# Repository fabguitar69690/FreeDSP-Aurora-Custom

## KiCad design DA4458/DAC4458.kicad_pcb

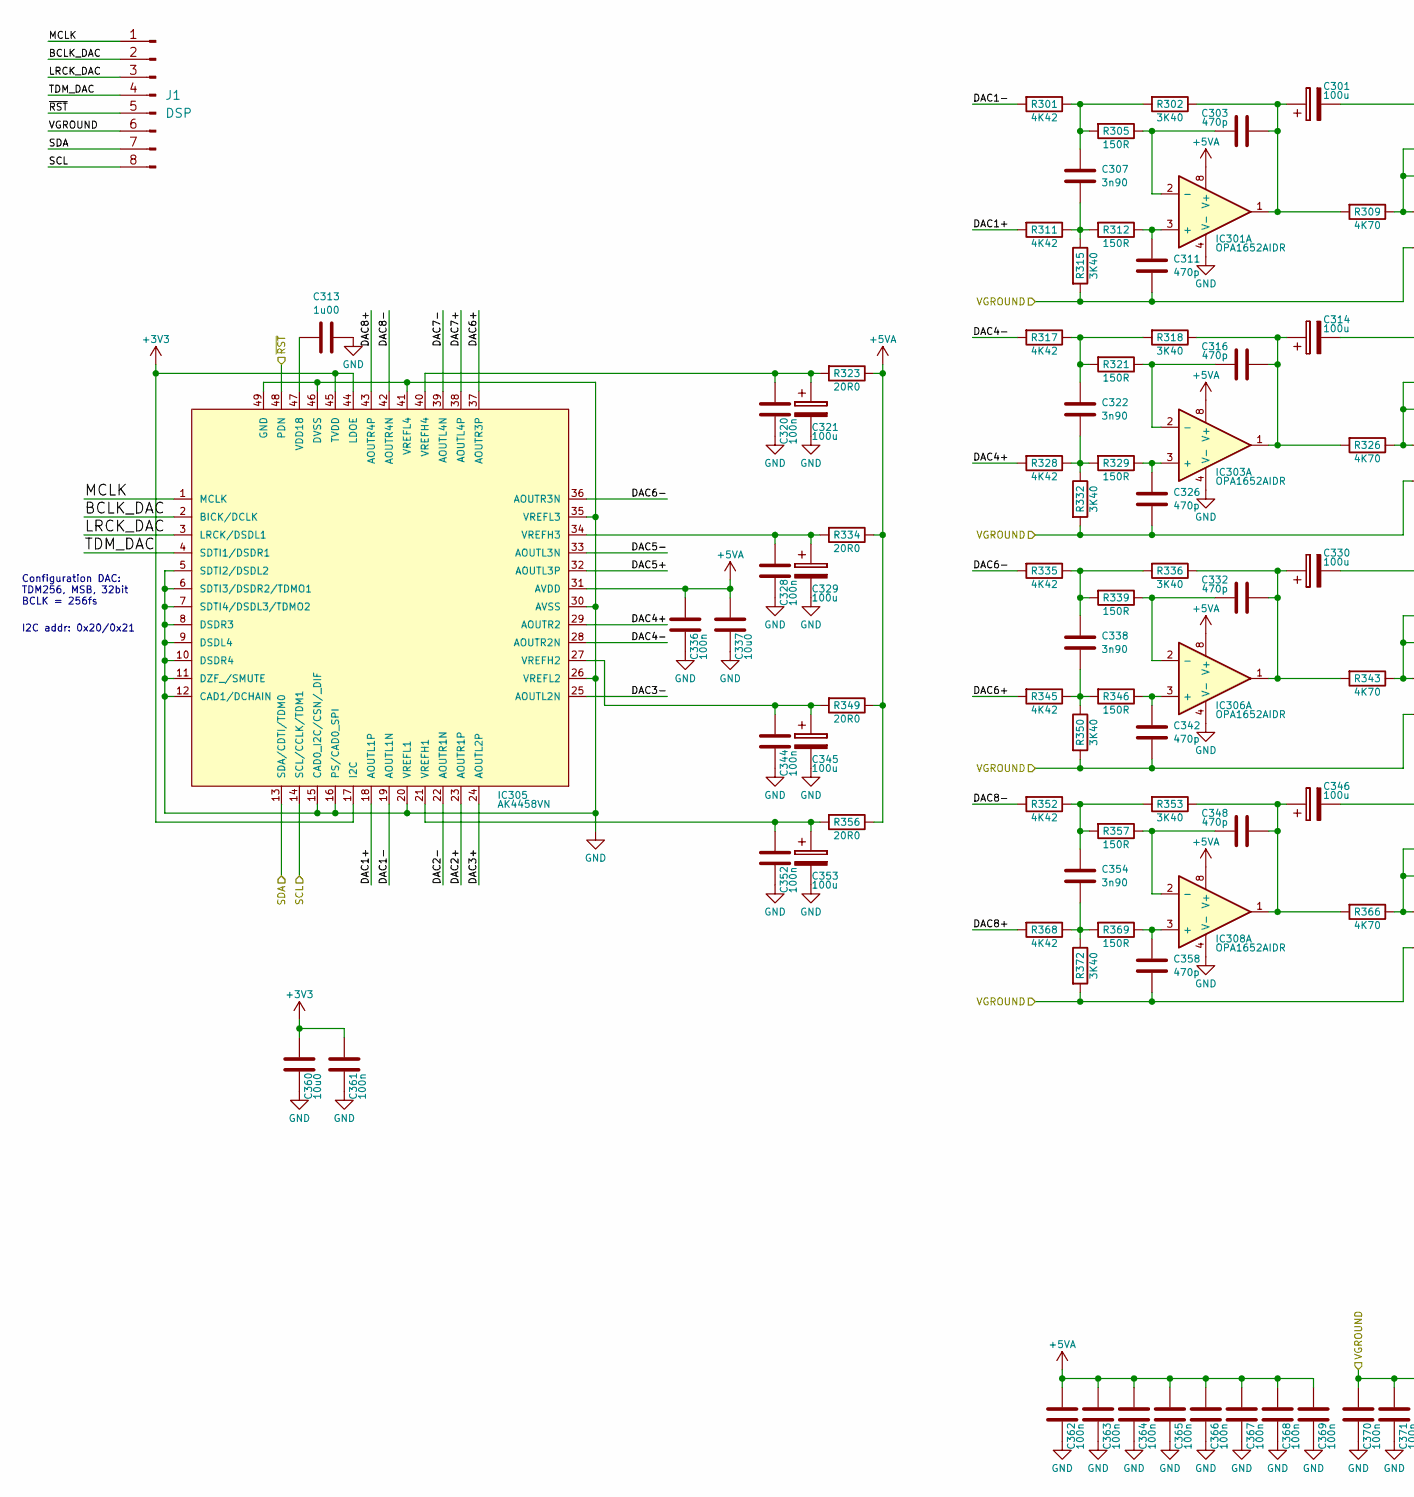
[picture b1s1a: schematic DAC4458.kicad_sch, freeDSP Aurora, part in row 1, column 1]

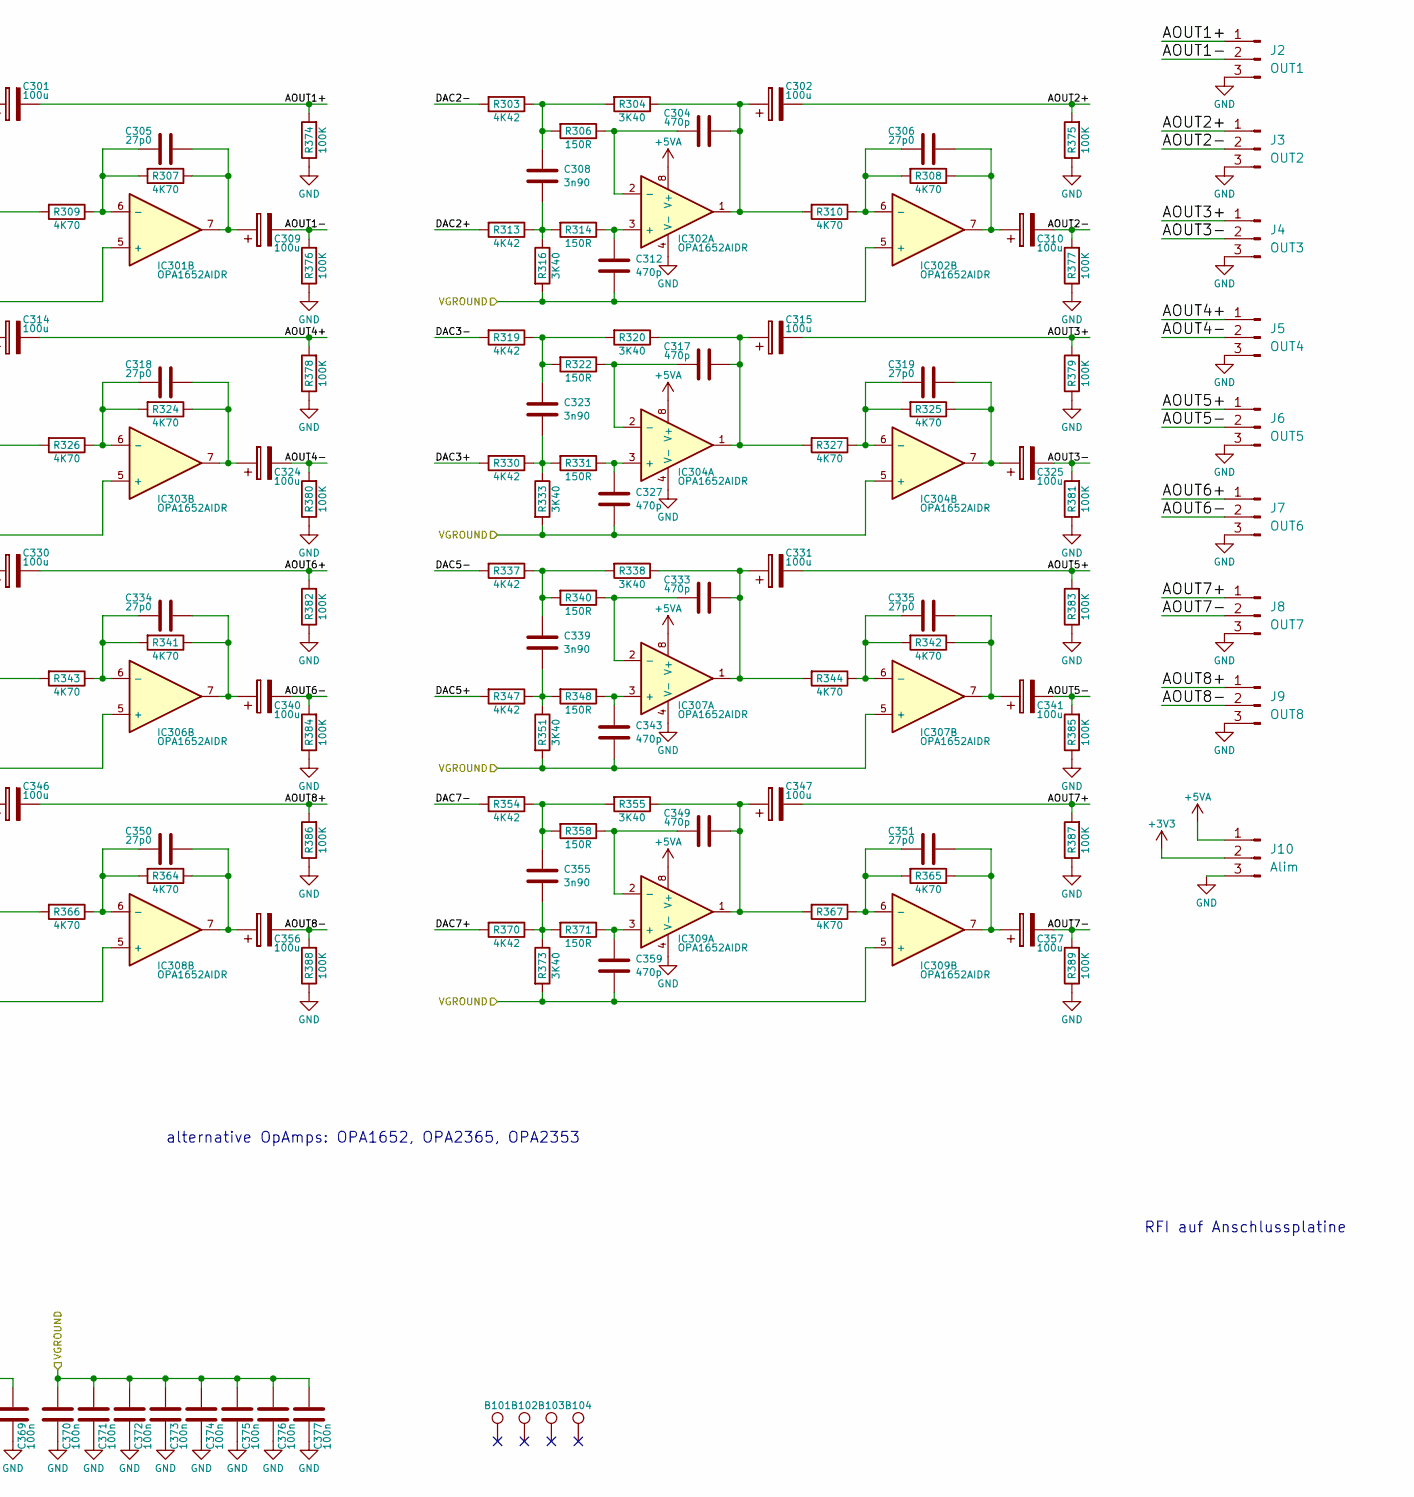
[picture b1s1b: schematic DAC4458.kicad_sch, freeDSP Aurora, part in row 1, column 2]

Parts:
B101, B102, B103, B104: TEST_1P; MountingHole_3.2mm_M3_DIN965_Pad
C301, C302, C309, C310, C314, C315, C321, C324, C325, C329, C330, C331, C340, C341, C345, C346, C347, C353, C356, C357: CAP_100u_20%_25V_ALUM_RADIAL; RD2_D5_L11; digikey UVY1E101MDD-ND
C303, C304, C311, C312, C316, C317, C326, C327, C332, C333, C342, C343, C348, C349, C358, C359: CAP_470p_2%_50V_PPS_0805; C0805-X7R; digikey PCF1292CT-ND
C305, C306, C318, C319, C334, C335, C350, C351: CAP_27p0_50V_C0G_NP0_0805; C0805-X7R; digikey 399-1114-1-ND
C307, C308, C322, C323, C338, C339, C354, C355: CAP_3n90_5%_16V_PPS_0805; C0805-X7R; digikey PCF1191CT-ND
C313: CAP_1u00_16V_X7R_0805; C0805-X7R; digikey 311-1365-1-ND
C320, C328, C336, C344, C352, C361, C362, C363, C364, C365, C366, C367, C368, C369, C370, C371, C372, C373, C374, C375, C376, C377: CAP_100n_50V_X7R_0805; C0805-X7R; digikey 399-1170-1-ND
C337, C360: CAP_10u0_25V_X5R_0805; C0805-X7R; digikey 490-10748-1-ND
IC301, IC302, IC303, IC304, IC306, IC307, IC308, IC309: IC_OPA1652AIDR; SOIC8_3.9x4.9mm_Pitch1.27mm; digikey 296-39101-1-ND
IC305: IC_AK4458VN; QFN48_7x7mm_Pitch0.5mm_EP_Handsoldering; digikey 974-1082-1-ND
J1: DSP; PinHeader_1x08_P2.54mm_Vertical
J2: OUT1; PinHeader_1x03_P2.54mm_Vertical
J3: OUT2; PinHeader_1x03_P2.54mm_Vertical
J4: OUT3; PinHeader_1x03_P2.54mm_Vertical
J5: OUT4; PinHeader_1x03_P2.54mm_Vertical
J6: OUT5; PinHeader_1x03_P2.54mm_Vertical
J7: OUT6; PinHeader_1x03_P2.54mm_Vertical
J8: OUT7; PinHeader_1x03_P2.54mm_Vertical
J9: OUT8; PinHeader_1x03_P2.54mm_Vertical
J10: Alim; PinHeader_1x03_P2.54mm_Vertical
R301, R303, R311, R313, R317, R319, R328, R330, R335, R337, R345, R347, R352, R354, R368, R370: RES_4K42_0.5%_0.1W_Thin_0805; C0805-RES; digikey RR12P4.42KDCT-ND
R302, R304, R315, R316, R318, R320, R332, R333, R336, R338, R350, R351, R353, R355, R372, R373: RES_3K40_0.5%_0.1W_Thin_0805; C0805-RES; digikey RR12P3.4KDCT-ND
R305, R306, R312, R314, R321, R322, R329, R331, R339, R340, R346, R348, R357, R358, R369, R371: RES_150R_1%_0.25W_Thin_0805; C0805-RES; digikey RNCP0805FTD150RCT-ND
R307, R308, R309, R310, R324, R325, R326, R327, R341, R342, R343, R344, R364, R365, R366, R367: RES_4K70_1%_0.125W_Thin_0805; C0805-RES; digikey YAG3364CT-ND
R323, R334, R349, R356: RES_20R0_1%_0.125W_Thick_0805; C0805-RES; digikey 311-20.0CRCT-ND
R374, R375, R376, R377, R378, R379, R380, R381, R382, R383, R384, R385, R386, R387, R388, R389: RES_100K_1%_0.125W_Thick_0805; C0805-RES; digikey 311-100KCRCT-ND

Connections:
+3V3: C360.1, C361.1, IC305.17 (I2C), IC305.44 (LDOE), IC305.45 (TVDD), J10.2
+5VA: C336.1, C337.1, C362.1, C363.1, C364.1, C365.1, C366.1, C367.1, C368.1, C369.1, IC301.8 (V+), IC302.8 (V+), IC303.8 (V+), IC304.8 (V+), IC305.31 (AVDD), IC306.8 (V+), IC307.8 (V+), IC308.8 (V+), IC309.8 (V+), J10.1, R323.1, R334.1, R349.1, R356.1
/AOUT1+: C301.2, J2.1, R374.2
/AOUT1-: C309.2, J2.2, R376.2
/AOUT2+: C302.2, J3.1, R375.2
/AOUT2-: C310.2, J3.2, R377.2
/AOUT3+: C315.2, J4.1, R379.2
/AOUT3-: C325.2, J4.2, R381.2
/AOUT4+: C314.2, J5.1, R378.2
/AOUT4-: C324.2, J5.2, R380.2
/AOUT5+: C331.2, J6.1, R383.2
/AOUT5-: C341.2, J6.2, R385.2
/AOUT6+: C330.2, J7.1, R382.2
/AOUT6-: C340.2, J7.2, R384.2
/AOUT7+: C347.2, J8.1, R387.2
/AOUT7-: C357.2, J8.2, R389.2
/AOUT8+: C346.2, J9.1, R386.2
/AOUT8-: C356.2, J9.2, R388.2
/BCLK_DAC: IC305.2 (BICK/DCLK), J1.2
/DAC1+: IC305.18 (AOUTL1P), R311.2
/DAC1-: IC305.19 (AOUTL1N), R301.2
/DAC2+: IC305.23 (AOUTR1P), R313.2
/DAC2-: IC305.22 (AOUTR1N), R303.2
/DAC3+: IC305.24 (AOUTL2P), R330.2
/DAC3-: IC305.25 (AOUTL2N), R319.2
/DAC4+: IC305.29 (AOUTR2), R328.2
/DAC4-: IC305.28 (AOUTR2N), R317.2
/DAC5+: IC305.32 (AOUTL3P), R347.2
/DAC5-: IC305.33 (AOUTL3N), R337.2
/DAC6+: IC305.37 (AOUTR3P), R345.2
/DAC6-: IC305.36 (AOUTR3N), R335.2
/DAC7+: IC305.38 (AOUTL4P), R370.2
/DAC7-: IC305.39 (AOUTL4N), R354.2
/DAC8+: IC305.43 (AOUTR4P), R368.2
/DAC8-: IC305.42 (AOUTR4N), R352.2
/LRCK_DAC: IC305.3 (LRCK/DSDL1), J1.3
/MCLK: IC305.1 (MCLK), J1.1
/SCL: IC305.14 (SCL/CCLK/TDM1), J1.8
/SDA: IC305.13 (SDA/CDTI/TDM0), J1.7
/TDM_DAC: IC305.4 (SDTI1/DSDR1), J1.4
/VGROUND: C311.2, C312.2, C326.2, C327.2, C342.2, C343.2, C358.2, C359.2, C370.1, C371.1, C372.1, C373.1, C374.1, C375.1, C376.1, C377.1, IC301.5 (+), IC302.5 (+), IC303.5 (+), IC304.5 (+), IC306.5 (+), IC307.5 (+), IC308.5 (+), IC309.5 (+), J1.6, R315.2, R316.2, R332.2, R333.2, R350.2, R351.2, R372.2, R373.2
/~RST: IC305.48 (PDN), J1.5
GND: C313.2, C320.2, C321.2, C328.2, C329.2, C336.2, C337.2, C344.2, C345.2, C352.2, C353.2, C360.2, C361.2, C362.2, C363.2, C364.2, C365.2, C366.2, C367.2, C368.2, C369.2, C370.2, C371.2, C372.2, C373.2, C374.2, C375.2, C376.2, C377.2, IC301.4 (V-), IC302.4 (V-), IC303.4 (V-), IC304.4 (V-), IC305.5 (SDTI2/DSDL2), IC305.6 (SDTI3/DSDR2/TDMO1), IC305.7 (SDTI4/DSDL3/TDMO2), IC305.8 (DSDR3), IC305.9 (DSDL4), IC305.10 (DSDR4), IC305.11 (DZF_/SMUTE), IC305.12 (CAD1/DCHAIN), IC305.15 (CAD0_I2C/CSN/_DIF), IC305.16 (PS/CAD0_SPI), IC305.20 (VREFL1), IC305.26 (VREFL2), IC305.30 (AVSS), IC305.35 (VREFL3), IC305.41 (VREFL4), IC305.46 (DVSS), IC305.49 (GND), IC306.4 (V-), IC307.4 (V-), IC308.4 (V-), IC309.4 (V-), J2.3, J3.3, J4.3, J5.3, J6.3, J7.3, J8.3, J9.3, J10.3, R374.1, R375.1, R376.1, R377.1, R378.1, R379.1, R380.1, R381.1, R382.1, R383.1, R384.1, R385.1, R386.1, R387.1, R388.1, R389.1
unnamed: C301.1, C303.1, IC301.1, R302.1, R309.2
unnamed: C302.1, C304.1, IC302.1, R304.1, R310.2
unnamed: C303.2, IC301.2 (-), R305.1
unnamed: C304.2, IC302.2 (-), R306.1
unnamed: C305.1, C309.1, IC301.7, R307.1
unnamed: C305.2, IC301.6 (-), R307.2, R309.1
unnamed: C306.1, C310.1, IC302.7, R308.1
unnamed: C306.2, IC302.6 (-), R308.2, R310.1
unnamed: C307.1, R301.1, R302.2, R305.2
unnamed: C307.2, R311.1, R312.2, R315.1
unnamed: C308.1, R303.1, R304.2, R306.2
unnamed: C308.2, R313.1, R314.2, R316.1
unnamed: C311.1, IC301.3 (+), R312.1
unnamed: C312.1, IC302.3 (+), R314.1
unnamed: C313.1, IC305.47 (VDD18)
unnamed: C314.1, C316.1, IC303.1, R318.1, R326.2
unnamed: C315.1, C317.1, IC304.1, R320.1, R327.2
unnamed: C316.2, IC303.2 (-), R321.1
unnamed: C317.2, IC304.2 (-), R322.1
unnamed: C318.1, C324.1, IC303.7, R324.1
unnamed: C318.2, IC303.6 (-), R324.2, R326.1
unnamed: C319.1, C325.1, IC304.7, R325.1
unnamed: C319.2, IC304.6 (-), R325.2, R327.1
unnamed: C320.1, C321.1, IC305.40 (VREFH4), R323.2
unnamed: C322.1, R317.1, R318.2, R321.2
unnamed: C322.2, R328.1, R329.2, R332.1
unnamed: C323.1, R319.1, R320.2, R322.2
unnamed: C323.2, R330.1, R331.2, R333.1
unnamed: C326.1, IC303.3 (+), R329.1
unnamed: C327.1, IC304.3 (+), R331.1
unnamed: C328.1, C329.1, IC305.34 (VREFH3), R334.2
unnamed: C330.1, C332.1, IC306.1, R336.1, R343.2
unnamed: C331.1, C333.1, IC307.1, R338.1, R344.2
unnamed: C332.2, IC306.2 (-), R339.1
unnamed: C333.2, IC307.2 (-), R340.1
unnamed: C334.1, C340.1, IC306.7, R341.1
unnamed: C334.2, IC306.6 (-), R341.2, R343.1
unnamed: C335.1, C341.1, IC307.7, R342.1
unnamed: C335.2, IC307.6 (-), R342.2, R344.1
unnamed: C338.1, R335.1, R336.2, R339.2
unnamed: C338.2, R345.1, R346.2, R350.1
unnamed: C339.1, R337.1, R338.2, R340.2
unnamed: C339.2, R347.1, R348.2, R351.1
unnamed: C342.1, IC306.3 (+), R346.1
unnamed: C343.1, IC307.3 (+), R348.1
unnamed: C344.1, C345.1, IC305.27 (VREFH2), R349.2
unnamed: C346.1, C348.1, IC308.1, R353.1, R366.2
unnamed: C347.1, C349.1, IC309.1, R355.1, R367.2
unnamed: C348.2, IC308.2 (-), R357.1
unnamed: C349.2, IC309.2 (-), R358.1
unnamed: C350.1, C356.1, IC308.7, R364.1
unnamed: C350.2, IC308.6 (-), R364.2, R366.1
unnamed: C351.1, C357.1, IC309.7, R365.1
unnamed: C351.2, IC309.6 (-), R365.2, R367.1
unnamed: C352.1, C353.1, IC305.21 (VREFH1), R356.2
unnamed: C354.1, R352.1, R353.2, R357.2
unnamed: C354.2, R368.1, R369.2, R372.1
unnamed: C355.1, R354.1, R355.2, R358.2
unnamed: C355.2, R370.1, R371.2, R373.1
unnamed: C358.1, IC308.3 (+), R369.1
unnamed: C359.1, IC309.3 (+), R371.1

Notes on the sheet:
alternative OpAmps: OPA1652, OPA2365, OPA2353
RFI auf Anschlussplatine
Configuration DAC: TDM256, MSB, 32bit BCLK = 256fs
I2C addr: 0x20/0x21

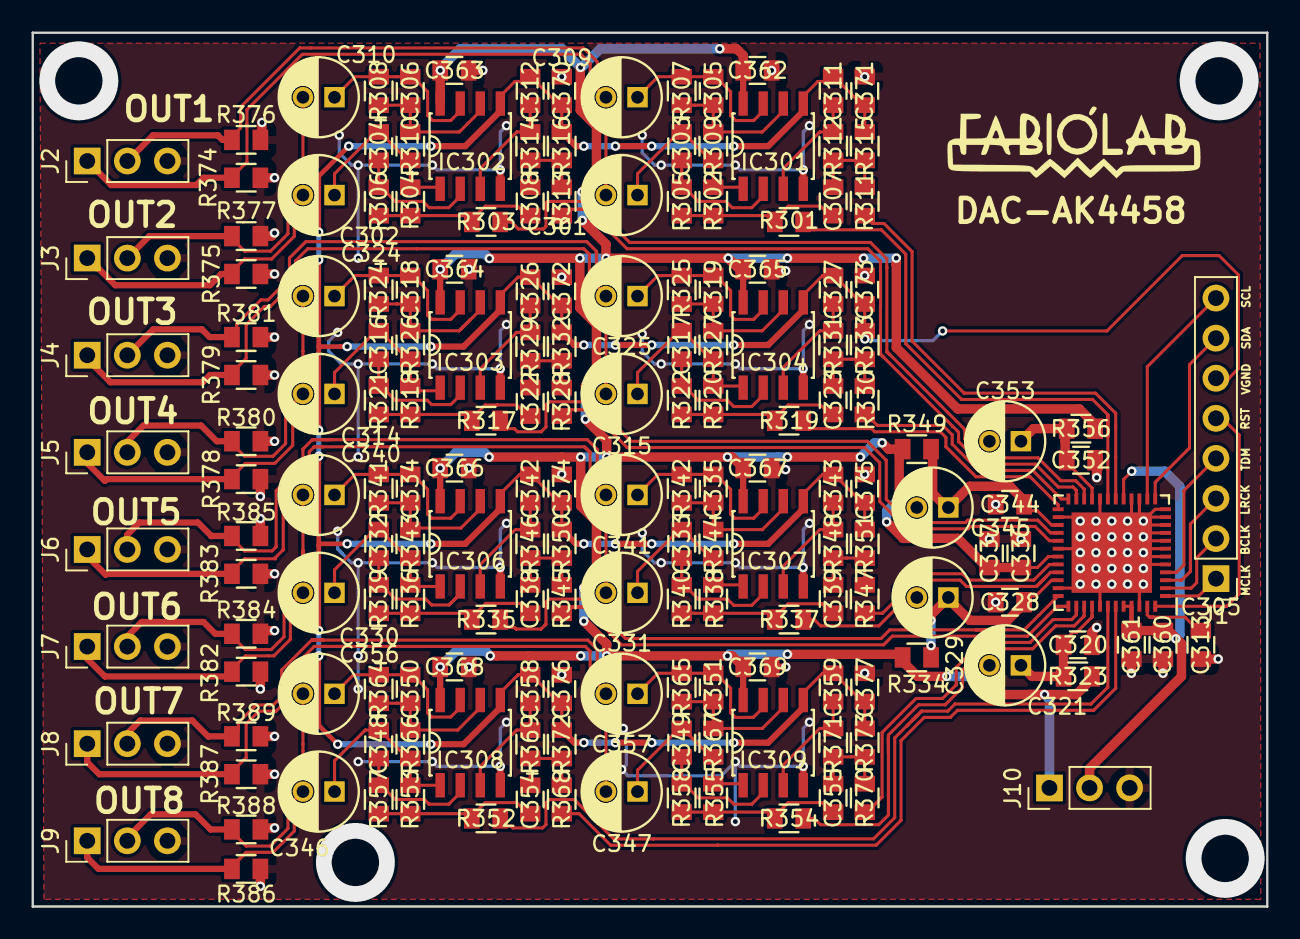
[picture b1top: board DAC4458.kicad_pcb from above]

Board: 2 copper layers, 78.2 x 55.4 mm, 180 parts (0 on the bottom side), 104 nets.

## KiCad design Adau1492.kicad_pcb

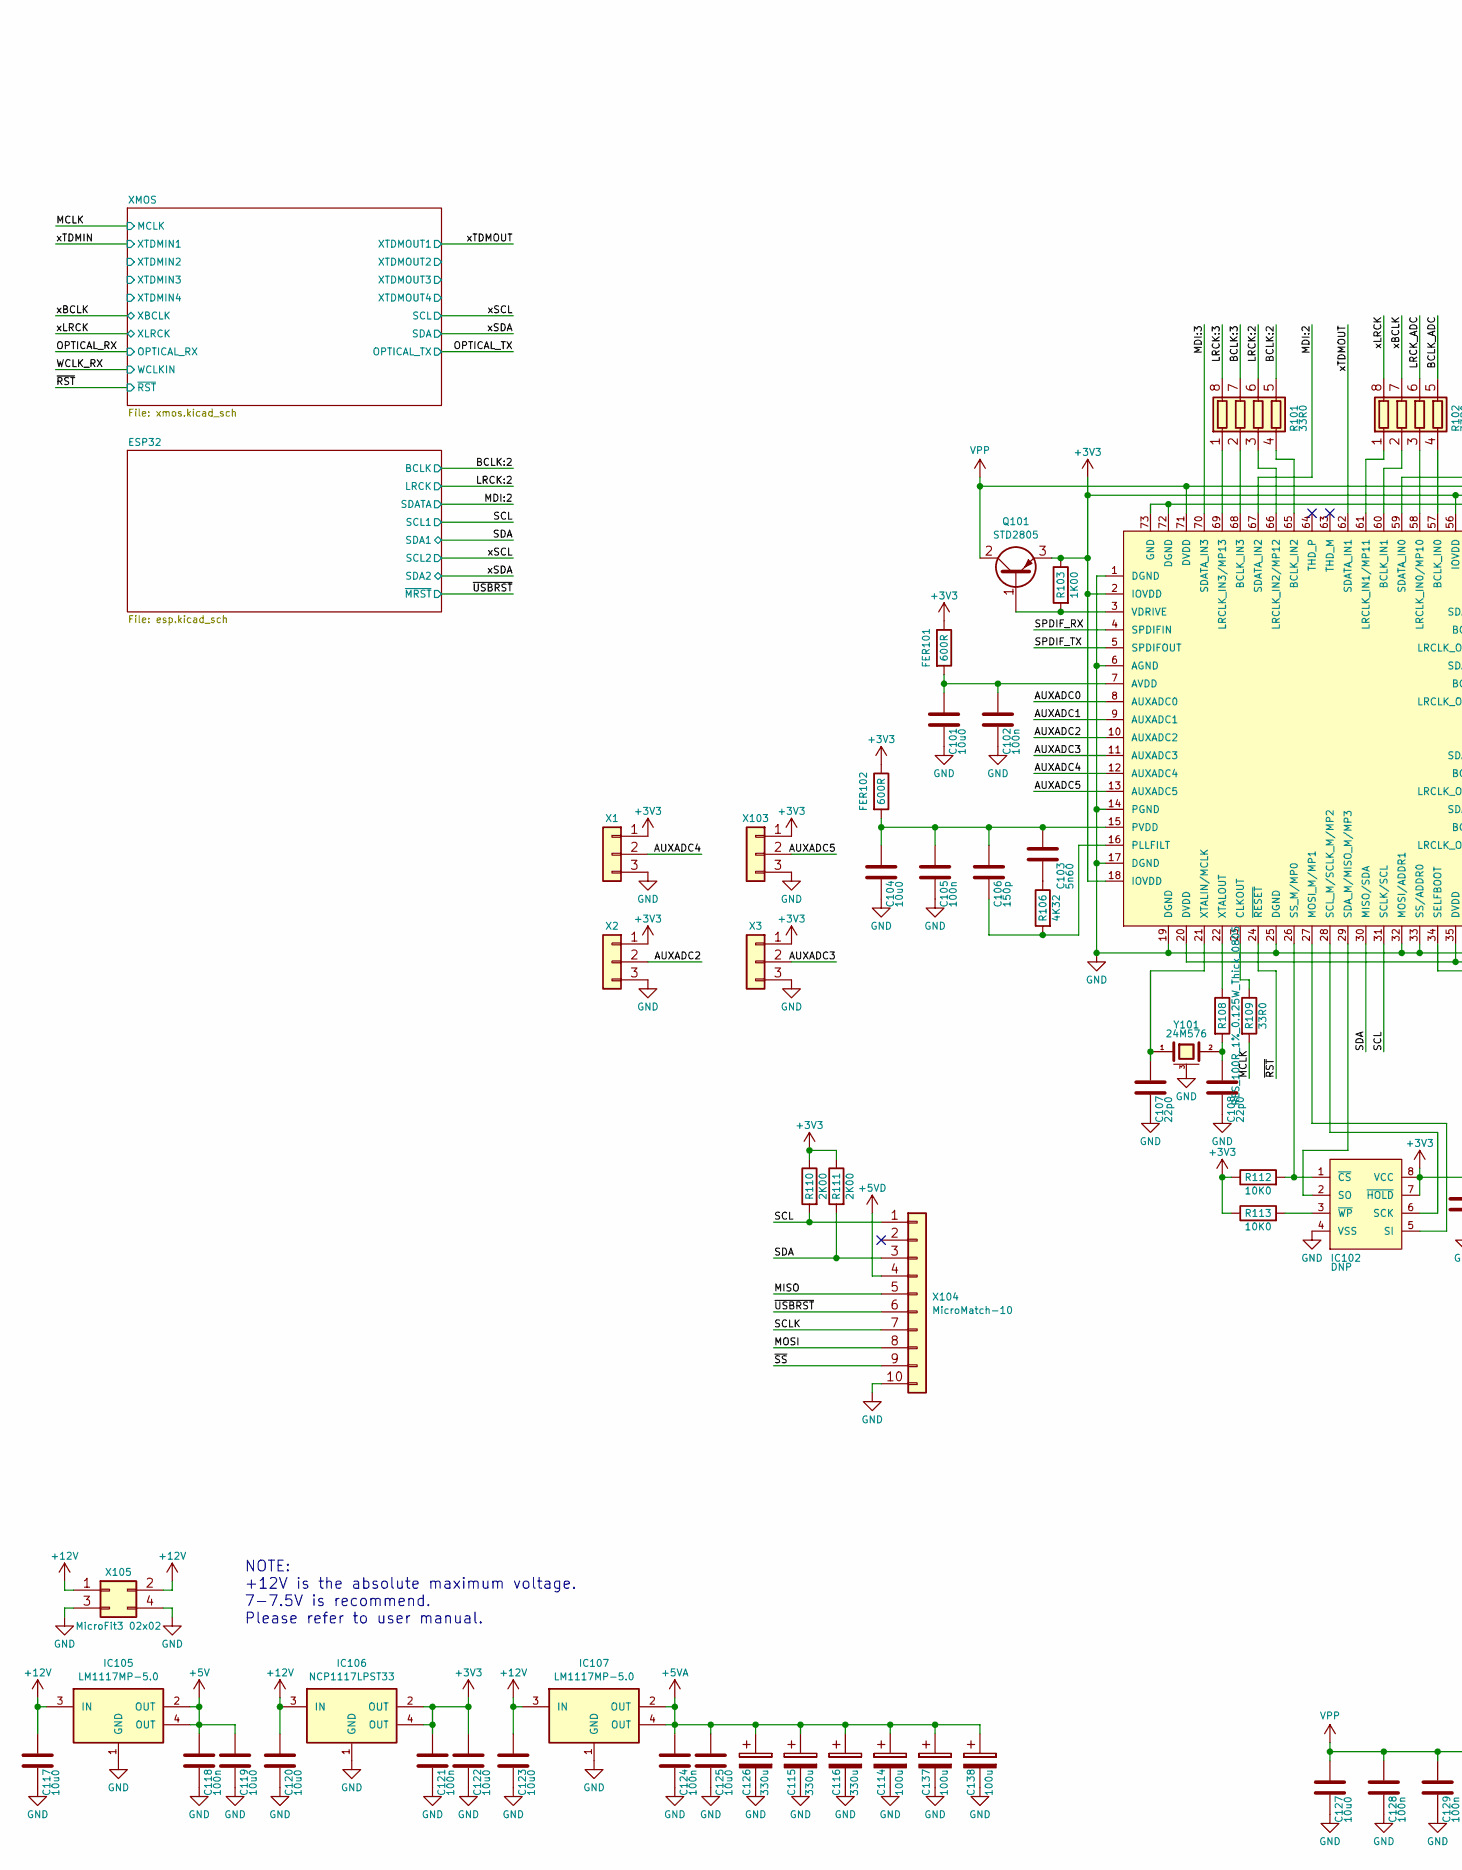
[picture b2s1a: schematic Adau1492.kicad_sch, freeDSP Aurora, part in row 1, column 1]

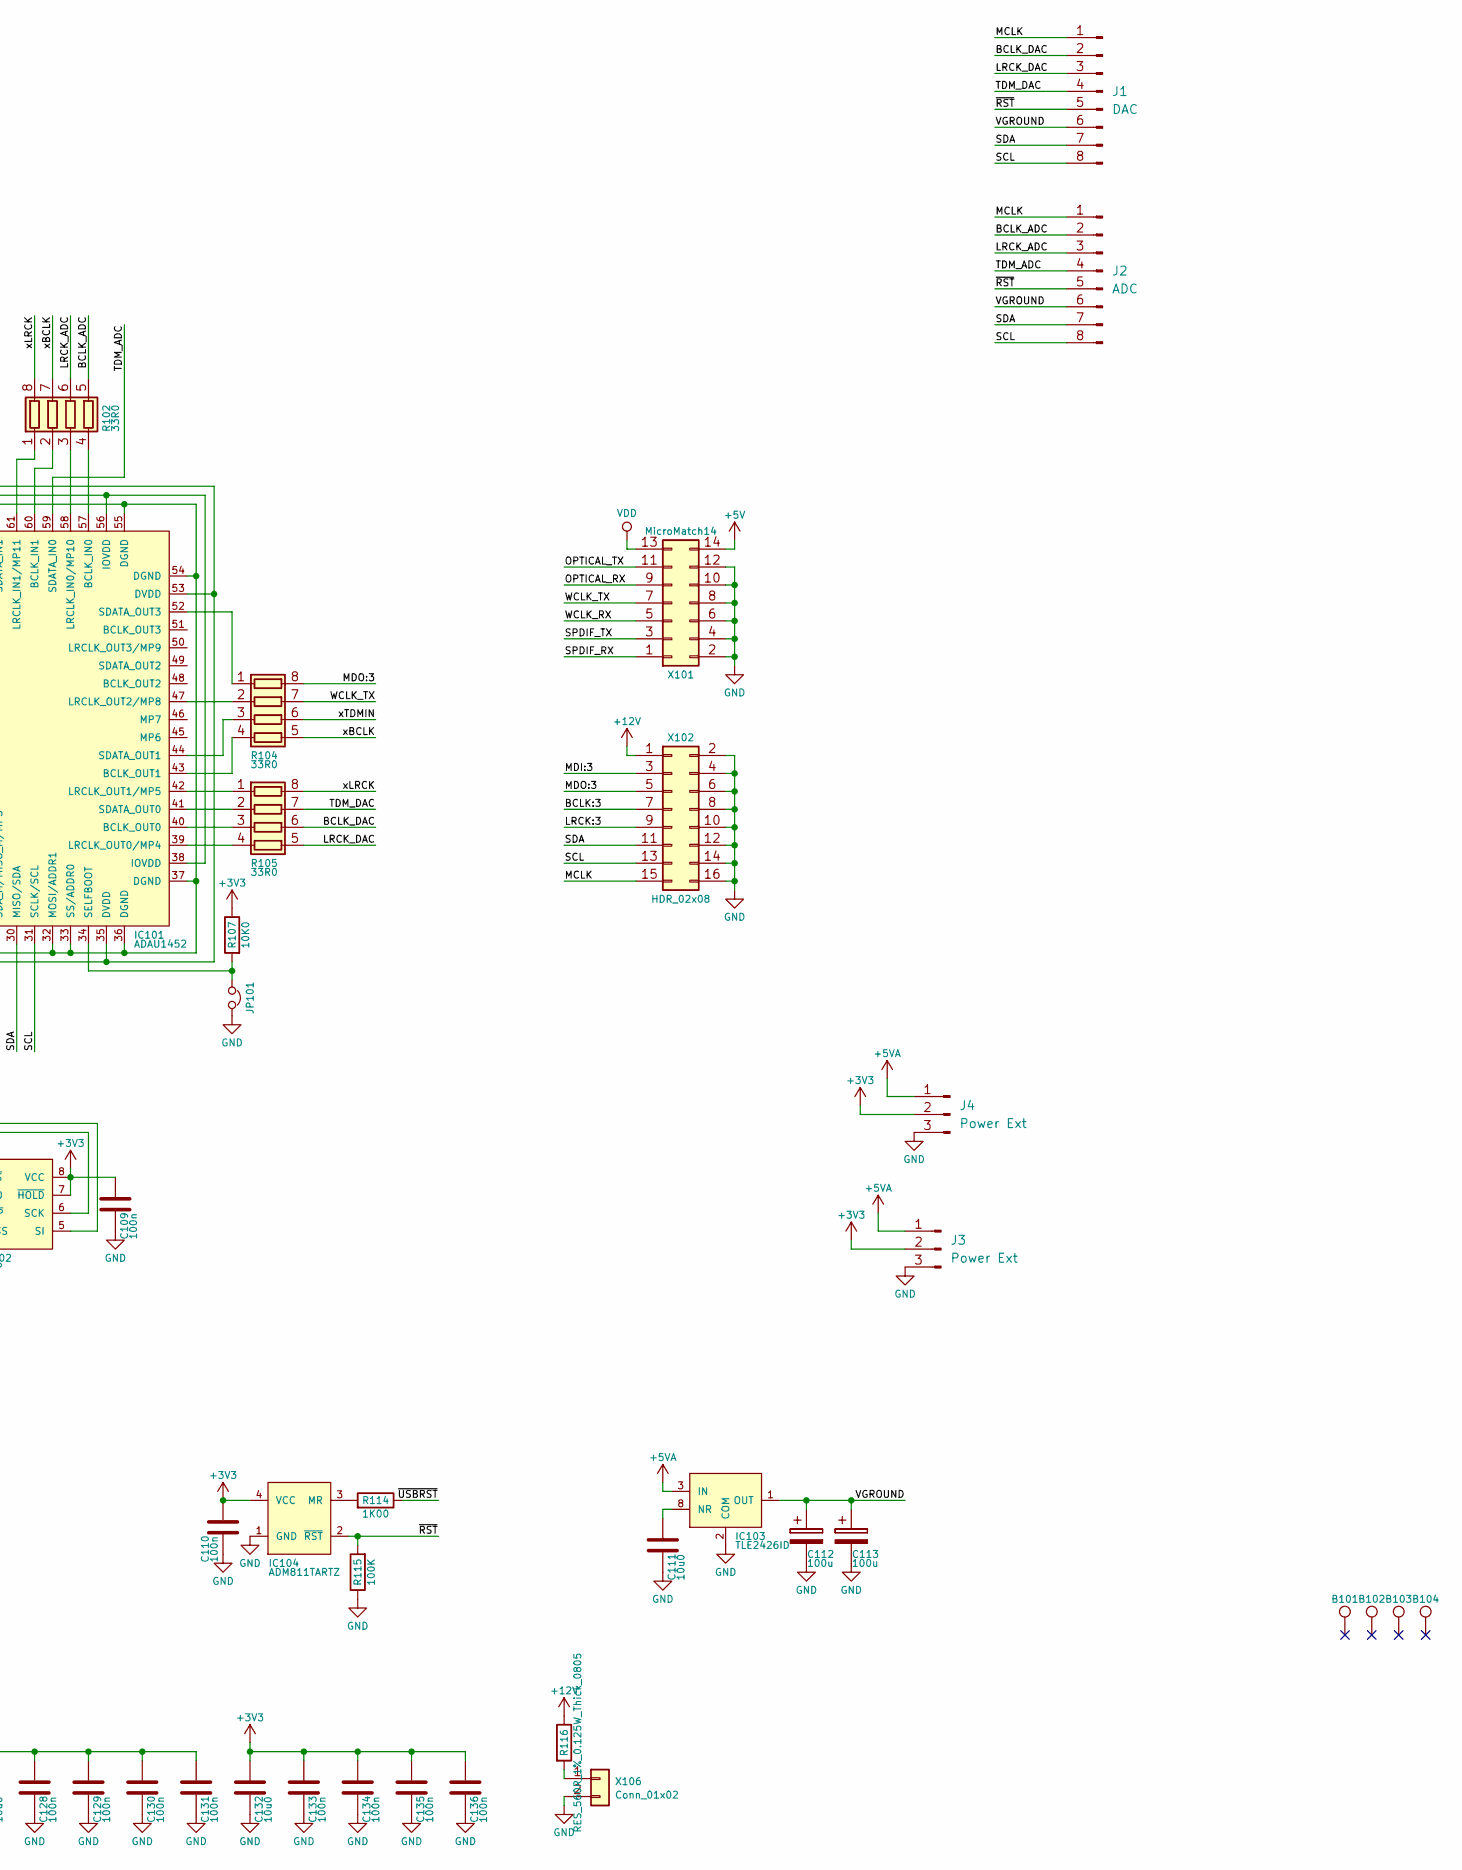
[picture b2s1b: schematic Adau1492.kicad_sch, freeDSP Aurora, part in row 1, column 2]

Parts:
B101, B102, B103, B104: TEST_1P; MountingHole_3.2mm_M3_DIN965_Pad
C101, C104, C111, C117, C119, C120, C122, C123, C125, C127, C132: CAP_10u0_25V_X5R_0805; C_0805_2012Metric_Pad1.18x1.45mm_HandSolder; digikey 490-10748-1-ND
C102, C105, C109, C110, C118, C121, C124, C128, C129, C130, C131, C133, C134, C135, C136: CAP_100n_50V_X7R_0805; C_0805_2012Metric_Pad1.18x1.45mm_HandSolder; digikey 399-1170-1-ND
C103: CAP_5n60_50V_X7R_0805; C_0805_2012Metric_Pad1.18x1.45mm_HandSolder; digikey 311-1134-1-ND
C106: CAP_150p_50V_C0G_0805; C_0805_2012Metric_Pad1.18x1.45mm_HandSolder; digikey 399-1125-1-ND
C107, C108: CAP_22p0_50V_C0G_NP0_0805; C_0805_2012Metric_Pad1.18x1.45mm_HandSolder; digikey 399-1113-1-ND
C112, C113, C114, C137, C138: CAP_100u_20%_25V_ALUM_RADIAL; CP_Radial_D5.0mm_P2.00mm; digikey UVY1E101MDD-ND
C115, C116, C126: 330u_20%_25V_ALUM_RADIAL; CP_Radial_D8.0mm_P3.50mm; digikey 732-8635-1-ND
FER101, FER102: FER_600R_600MA_0805; R_0805_2012Metric_Pad1.20x1.40mm_HandSolder; digikey 490-1040-1-ND
IC101: IC_ADAU1452; LFCSP-72-1EP_10x10mm_P0.5mm_EP5.3x5.3mm_ThermalVias; digikey ADAU1452WBCPZ-ND
IC102: IC_25AA1024; SOIC127P794X203-8N; digikey 25AA1024T-I/SMCT-ND
IC103: IC_TLE2426ID; SOIC-8-1EP_3.9x4.9mm_P1.27mm_EP2.29x3mm; digikey 296-1345-1-ND
IC104: IC_ADM811TARTZ; SOT-143_Handsoldering; digikey ADM811TARTZ-REELCT-ND
IC105, IC107: IC_LM1117MP-5.0; SOT-223; digikey LM1117MP-5.0/NOPBCT-ND
IC106: IC_NCP1117LPST33; SOT-223; digikey NCP1117LPST33T3GOSCT-ND
J1: DAC; PinHeader_1x08_P2.54mm_Vertical
J2: ADC; PinHeader_1x08_P2.54mm_Vertical
J3, J4: Power Ext; PinHeader_1x03_P2.54mm_Vertical
JP101: CON_JUMPER; PinSocket_1x02_P2.54mm_Vertical; digikey 732-5315-ND
Q101: Q_STD2805; TO-252-2; digikey 497-7465-1-ND
R101, R102, R104, R105: 33R0_5%_4x0603; R_Array_Convex_4x0603; digikey TC164J-33CT-ND
R103, R114: RES_1K00_1%_0.125W_Thick_0805; R_0805_2012Metric_Pad1.20x1.40mm_HandSolder; digikey 311-1.00KCRCT-ND
R106: RES_4K32_1%_0.125W_Thick_0805; R_0805_2012Metric_Pad1.20x1.40mm_HandSolder; digikey 311-4.32KCRCT-ND
R107, R112, R113: RES_10K0_1%_0.125W_Thick_0805; R_0805_2012Metric_Pad1.20x1.40mm_HandSolder; digikey 311-10.0KCRCT-ND
R108: RES_100R_1%_0.125W_Thick_0805; R_0805_2012Metric_Pad1.20x1.40mm_HandSolder; digikey 311-100CRCT-ND
R109: RES_33R0_1%_0.125W_Thick_0805; R_0805_2012Metric_Pad1.20x1.40mm_HandSolder; digikey 311-33.0CRCT-ND
R110, R111: RES_2K00_1%_0.125W_Thick_0805; R_0805_2012Metric_Pad1.20x1.40mm_HandSolder; digikey 311-2.00KCRCT-ND
R115: RES_100K_1%_0.125W_Thick_0805; R_0805_2012Metric_Pad1.20x1.40mm_HandSolder; digikey 311-100KCRCT-ND
R116: RES_560R_1%_0.125W_Thick_0805; R_0805_2012Metric_Pad1.20x1.40mm_HandSolder; digikey 311-560CRCT-ND
X1, X2, X3, X103: Conn_01x03; PinSocket_1x03_P2.54mm_Vertical; digikey WM1732-ND
X101: MicroMatch14; PinSocket_2x07_P2.54mm_Vertical; digikey A110871CT-ND
X102: HDR_02x08; PinSocket_2x08_P2.54mm_Vertical; digikey S2011EC-08-ND
X104: CON_MicroMatch-10G; PinSocket_2x05_P2.54mm_Vertical; digikey A110869-ND
X105: CON_MicroFit3_02x02; PinSocket_2x02_P2.54mm_Vertical; digikey WM10670-ND
X106: Conn_01x02; PinSocket_1x02_P2.54mm_Vertical; digikey 732-5315-ND
Y101: 24M576; XRCGB24M576F3M02R0; digikey SER3690CT-ND

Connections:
+3V3: C109.1, C110.1, C121.1, C122.1, C132.1, C133.1, C134.1, C135.1, C136.1, FER101.1, FER102.1, IC101.2 (IOVDD), IC101.18 (IOVDD), IC101.38 (IOVDD), IC101.56 (IOVDD), IC102.7 (~HOLD), IC102.8 (VCC), IC104.4 (VCC), IC106.2 (OUT), IC106.4 (OUT), J3.2, J4.2, Q101.3 (E), R103.1, R107.1, R110.1, R111.1, R112.1, R113.1, X1.1, X2.1, X3.1, X103.1; also elsewhere on the board
+5V: C118.1, C119.1, IC105.2 (OUT), IC105.4 (OUT), X101.14; also elsewhere on the board
+5VA: C114.1, C115.1, C116.1, C124.1, C125.1, C126.1, C137.1, C138.1, IC103.3 (IN), IC107.2 (OUT), IC107.4 (OUT), J3.1, J4.1
+5VD: X104.4
+12V: C117.1, C120.1, C123.1, IC105.3 (IN), IC106.3 (IN), IC107.3 (IN), R116.1, X102.1, X105.1, X105.2; also elsewhere on the board
/AUXADC0: IC101.8 (AUXADC0)
/AUXADC1: IC101.9 (AUXADC1)
/AUXADC2: IC101.10 (AUXADC2), X2.2; also elsewhere on the board
/AUXADC3: IC101.11 (AUXADC3), X3.2; also elsewhere on the board
/AUXADC4: IC101.12 (AUXADC4), X1.2; also elsewhere on the board
/AUXADC5: IC101.13 (AUXADC5), X103.2; also elsewhere on the board
/BCLK:2: R101.5 (R4.2); also elsewhere on the board
/BCLK:3: R101.7 (R2.2), X102.7
/BCLK_ADC: J2.2, R102.5 (R4.2)
/BCLK_DAC: J1.2, R105.6 (R3.2)
/LRCK:2: R101.6 (R3.2); also elsewhere on the board
/LRCK:3: R101.8 (R1.2), X102.9
/LRCK_ADC: J2.3, R102.6 (R3.2)
/LRCK_DAC: J1.3, R105.5 (R4.2)
/MCLK: J1.1, J2.1, R109.2, X102.15; also elsewhere on the board
/MDI:2: IC101.67 (SDATA_IN2); also elsewhere on the board
/MDI:3: IC101.70 (SDATA_IN3), X102.3
/MDO:3: R104.8 (R1.2), X102.5
/MISO: X104.5
/MOSI: X104.8
/OPTICAL_RX: X101.9; also elsewhere on the board
/OPTICAL_TX: X101.11; also elsewhere on the board
/SCL: IC101.31 (SCLK/SCL), J1.8, J2.8, R110.2, X102.13, X104.1; also elsewhere on the board
/SCLK: X104.7
/SDA: IC101.30 (MISO/SDA), J1.7, J2.7, R111.2, X102.11, X104.3; also elsewhere on the board
/SPDIF_RX: IC101.4 (SPDIFIN), X101.1
/SPDIF_TX: IC101.5 (SPDIFOUT), X101.3
/TDM_ADC: IC101.59 (SDATA_IN0), J2.4
/TDM_DAC: J1.4, R105.7 (R2.2)
/VGROUND: C112.1, C113.1, IC103.1 (OUT), J1.6, J2.6
/WCLK_RX: X101.5; also elsewhere on the board
/WCLK_TX: R104.7 (R2.2), X101.7
/xBCLK: R102.7 (R2.2), R104.5 (R4.2); also elsewhere on the board
/xLRCK: R102.8 (R1.2), R105.8 (R1.2); also elsewhere on the board
/xTDMIN: R104.6 (R3.2); also elsewhere on the board
/xTDMOUT: IC101.62 (SDATA_IN1); also elsewhere on the board
/~RST: IC101.24 (~RESET), IC104.2 (~RST), J1.5, J2.5, R115.2; also elsewhere on the board
/~SS: X104.9
/~USBRST: R114.1, X104.6; also elsewhere on the board
GND: C101.2, C102.2, C104.2, C105.2, C107.2, C108.2, C109.2, C110.2, C111.2, C112.2, C113.2, C114.2, C115.2, C116.2, C117.2, C118.2, C119.2, C120.2, C121.2, C122.2, C123.2, C124.2, C125.2, C126.2, C127.2, C128.2, C129.2, C130.2, C131.2, C132.2, C133.2, C134.2, C135.2, C136.2, C137.2, C138.2, IC101.1 (DGND), IC101.6 (AGND), IC101.14 (PGND), IC101.17 (DGND), IC101.19 (DGND), IC101.25 (DGND), IC101.32 (MOSI/ADDR1), IC101.33 (SS/ADDR0), IC101.36 (DGND), IC101.37 (DGND), IC101.54 (DGND), IC101.55 (DGND), IC101.72 (DGND), IC101.73 (GND), IC102.4 (VSS), IC103.2 (COM), IC104.1 (GND), IC105.1 (GND), IC106.1 (GND), IC107.1 (GND), J3.3, J4.3, JP101.2, R115.1, X1.3, X2.3, X3.3, X101.2, X101.4, X101.6, X101.8, X101.10, X101.12, X102.2, X102.4, X102.6, X102.8, X102.10, X102.12, X102.14, X102.16, X103.3, X104.10, X105.3, X105.4, X106.2, Y101.3 (case); also elsewhere on the board
unnamed: C101.1, C102.1, FER101.2, IC101.7 (AVDD)
unnamed: C103.1, C104.1, C105.1, C106.1, FER102.2, IC101.15 (PVDD)
unnamed: C103.2, R106.1
unnamed: C106.2, IC101.16 (PLLFILT), R106.2
unnamed: C107.1, IC101.21 (XTALIN/MCLK), Y101.1
unnamed: C108.1, R108.2, Y101.2
unnamed: C111.1, IC103.8 (NR)
unnamed: IC101.3 (VDRIVE), Q101.1 (B), R103.2
unnamed: IC101.22 (XTALOUT), R108.1
unnamed: IC101.23 (CLKOUT), R109.1
unnamed: IC101.26 (SS_M/MP0), IC102.1 (~CS), R112.2
unnamed: IC101.27 (MOSI_M/MP1), IC102.5 (SI)
unnamed: IC101.28 (SCL_M/SCLK_M/MP2), IC102.6 (SCK)
unnamed: IC101.29 (SDA_M/MISO_M/MP3), IC102.2 (SO)
unnamed: IC101.34 (SELFBOOT), JP101.1, R107.2
unnamed: IC101.39 (LRCLK_OUT0/MP4), R105.4 (R4.1)
unnamed: IC101.40 (BCLK_OUT0), R105.3 (R3.1)
unnamed: IC101.41 (SDATA_OUT0), R105.2 (R2.1)
unnamed: IC101.42 (LRCLK_OUT1/MP5), R105.1 (R1.1)
unnamed: IC101.43 (BCLK_OUT1), R104.4 (R4.1)
unnamed: IC101.44 (SDATA_OUT1), R104.3 (R3.1)
unnamed: IC101.47 (LRCLK_OUT2/MP8), R104.2 (R2.1)
unnamed: IC101.52 (SDATA_OUT3), R104.1 (R1.1)
unnamed: IC101.57 (BCLK_IN0), R102.4 (R4.1)
unnamed: IC101.58 (LRCLK_IN0/MP10), R102.3 (R3.1)
unnamed: IC101.60 (BCLK_IN1), R102.2 (R2.1)
unnamed: IC101.61 (LRCLK_IN1/MP11), R102.1 (R1.1)
unnamed: IC101.65 (BCLK_IN2), R101.4 (R4.1)
unnamed: IC101.66 (LRCLK_IN2/MP12), R101.3 (R3.1)
unnamed: IC101.68 (BCLK_IN3), R101.2 (R2.1)
unnamed: IC101.69 (LRCLK_IN3/MP13), R101.1 (R1.1)
unnamed: IC102.3 (~WP), R113.2
unnamed: IC104.3 (MR), R114.2
unnamed: R116.2, X106.1
VDD: X101.13; also elsewhere on the board
VPP: C127.1, C128.1, C129.1, C130.1, C131.1, IC101.20 (DVDD), IC101.35 (DVDD), IC101.53 (DVDD), IC101.71 (DVDD), Q101.2 (C)

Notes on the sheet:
NOTE: +12V is the absolute maximum voltage. 7-7.5V is recommend. Please refer to user manual.
